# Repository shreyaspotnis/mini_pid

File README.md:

# mini_pid

A dual Proportional - Integral servo box

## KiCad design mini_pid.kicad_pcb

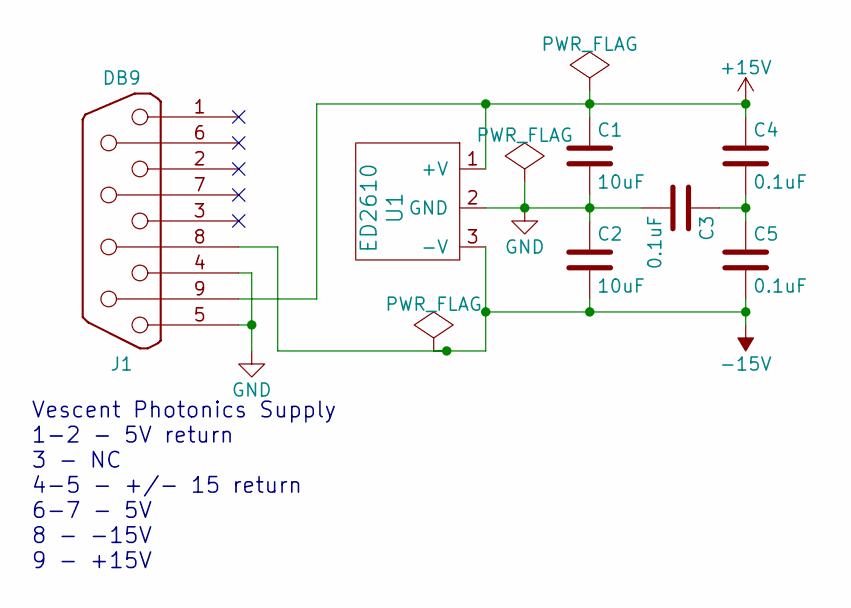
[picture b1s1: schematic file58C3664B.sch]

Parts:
C1, C2: 10uF; C_0805_HandSoldering
C3, C4, C5: 0.1uF; C_0805_HandSoldering
J1: DB9; DB9_Throughhole
U1: ED2610

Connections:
+15V: C1.1, C4.1, J1.9, U1.1 (+V); also elsewhere on the board
-15V: C2.2, C5.2, J1.8, U1.3 (-V); also elsewhere on the board
GND: C1.2, C2.1, C3.2, J1.4, J1.5, U1.2 (GND); also elsewhere on the board
unnamed: C3.1, C4.2, C5.1

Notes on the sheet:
Vescent Photonics Supply 1-2 - 5V return 3 - NC 4-5 - +/- 15 return 6-7 - 5V 8 - -15V 9 - +15V

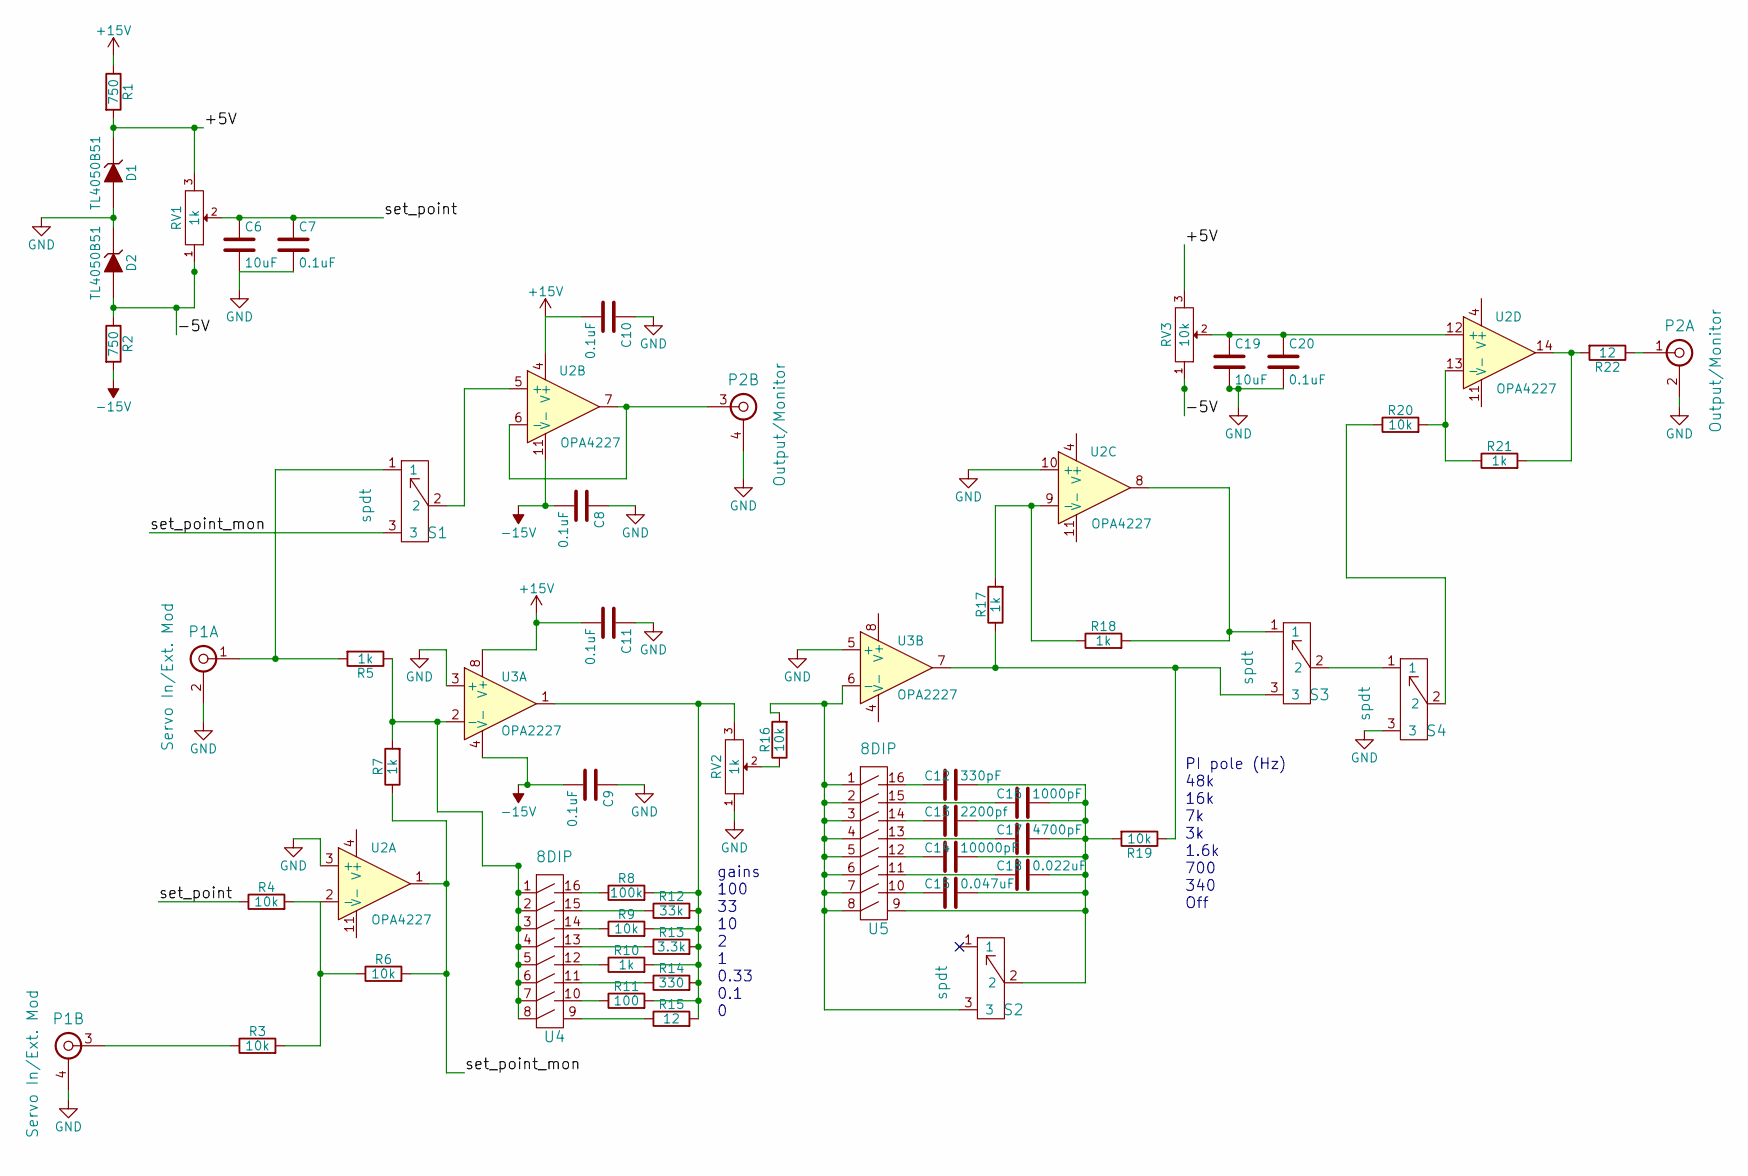
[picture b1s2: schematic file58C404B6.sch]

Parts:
C6, C19: 10uF; C_0805_HandSoldering
C7, C8, C9, C10, C11, C20: 0.1uF; C_0805_HandSoldering
C12: 330pF; C_0805_HandSoldering
C13: 2200pf; C_0805_HandSoldering
C14: 10000pF; C_0805_HandSoldering
C15: 0.047uF; C_0805_HandSoldering
C16: 1000pF; C_0805_HandSoldering
C17: 4700pF; C_0805_HandSoldering
C18: 0.022uF; C_0805_HandSoldering
D1, D2: TL4050B51; SOT-23
P1: Servo In/Ext. Mod; Dual-BNC-ARF2136
P2: Output/Monitor; Dual-BNC-ARF2136
R1, R2: 750; R_0805_HandSoldering
R3, R4, R6, R9, R16, R19, R20: 10k; R_0805_HandSoldering
R5, R7, R10, R17, R18, R21: 1k; R_0805_HandSoldering
R8: 100k; R_0805_HandSoldering
R11: 100; R_0805_HandSoldering
R12: 33k; R_0805_HandSoldering
R13: 3.3k; R_0805_HandSoldering
R14: 330; R_0805_HandSoldering
R15, R22: 12; R_0805_HandSoldering
RV1, RV2: 1k; VishaySpectrol536
RV3: 10k; VishaySpectrol536
S1, S2, S4: spdt; SPDT-Horizontal
S3: spdt; CJS-1200TB-SPDT
U2: OPA4227; SOIC-14_3.9x8.7mm_Pitch1.27mm
U3: OPA2227; SOIC-8_3.9x4.9mm_Pitch1.27mm
U4, U5: 8DIP; 8_POS_DIP_Switch

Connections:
+15V: C10.2, C11.2, R1.1, U2.4 (V+), U3.8 (V+); also elsewhere on the board
-15V: C8.2, C9.2, R2.2, U2.11 (V-), U3.4 (V-); also elsewhere on the board
/PI Circuit 1/+5V: D1.1 (K), R1.2, RV1.3, RV3.3
/PI Circuit 1/-5V: D2.2 (A), R2.1, RV1.1, RV3.1
/PI Circuit 1/set_point: C6.1, C7.1, R4.1, RV1.2
/PI Circuit 1/set_point_mon: R6.2, R7.1, S1.3, U2.1
GND: C6.2, C7.2, C8.1, C9.1, C10.1, C11.1, C19.2, C20.2, D1.2 (A), D2.1 (K), P1.2, P1.4, P2.2, P2.4, RV2.1, S4.3, U2.3 (+), U2.10 (+), U3.3 (+), U3.5 (+); also elsewhere on the board
unnamed: C12.1, C13.1, C14.1, C15.1, C16.1, C17.1, C18.1, R19.2, S2.2, U5.9
unnamed: C12.2, U5.16
unnamed: C13.2, U5.14
unnamed: C14.2, U5.12
unnamed: C15.2, U5.10
unnamed: C16.2, U5.15
unnamed: C17.2, U5.13
unnamed: C18.2, U5.11
unnamed: C19.1, C20.1, RV3.2, U2.12 (+)
unnamed: P1.1, R5.2, S1.1
unnamed: P1.3, R3.1
unnamed: P2.1, R22.1
unnamed: P2.3, U2.6 (-), U2.7
unnamed: R3.2, R4.2, R6.1, U2.2 (-)
unnamed: R5.1, R7.2, U3.2 (-), U4.1, U4.2, U4.3, U4.4, U4.5, U4.6, U4.7, U4.8
unnamed: R8.1, U4.16
unnamed: R9.1, U4.14
unnamed: R10.1, U4.12
unnamed: R8.2, R9.2, R10.2, R11.2, R12.2, R13.2, R14.2, R15.2, RV2.3, U3.1
unnamed: R11.1, U4.10
unnamed: R12.1, U4.15
unnamed: R13.1, U4.13
unnamed: R14.1, U4.11
unnamed: R15.1, U4.9
unnamed: R16.1, RV2.2
unnamed: R16.2, S2.3, U3.6 (-), U5.1, U5.2, U5.3, U5.4, U5.5, U5.6, U5.7, U5.8
unnamed: R17.1, R19.1, S3.3, U3.7
unnamed: R17.2, R18.1, U2.9 (-)
unnamed: R18.2, S3.1, U2.8
unnamed: R20.1, S4.2
unnamed: R20.2, R21.1, U2.13 (-)
unnamed: R21.2, R22.2, U2.14
unnamed: S1.2, U2.5 (+)
unnamed: S3.2, S4.1

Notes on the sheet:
gains 100 33 10 2 1 0.33 0.1 0
PI pole (Hz) 48k 16k 7k 3k 1.6k 700 340 Off

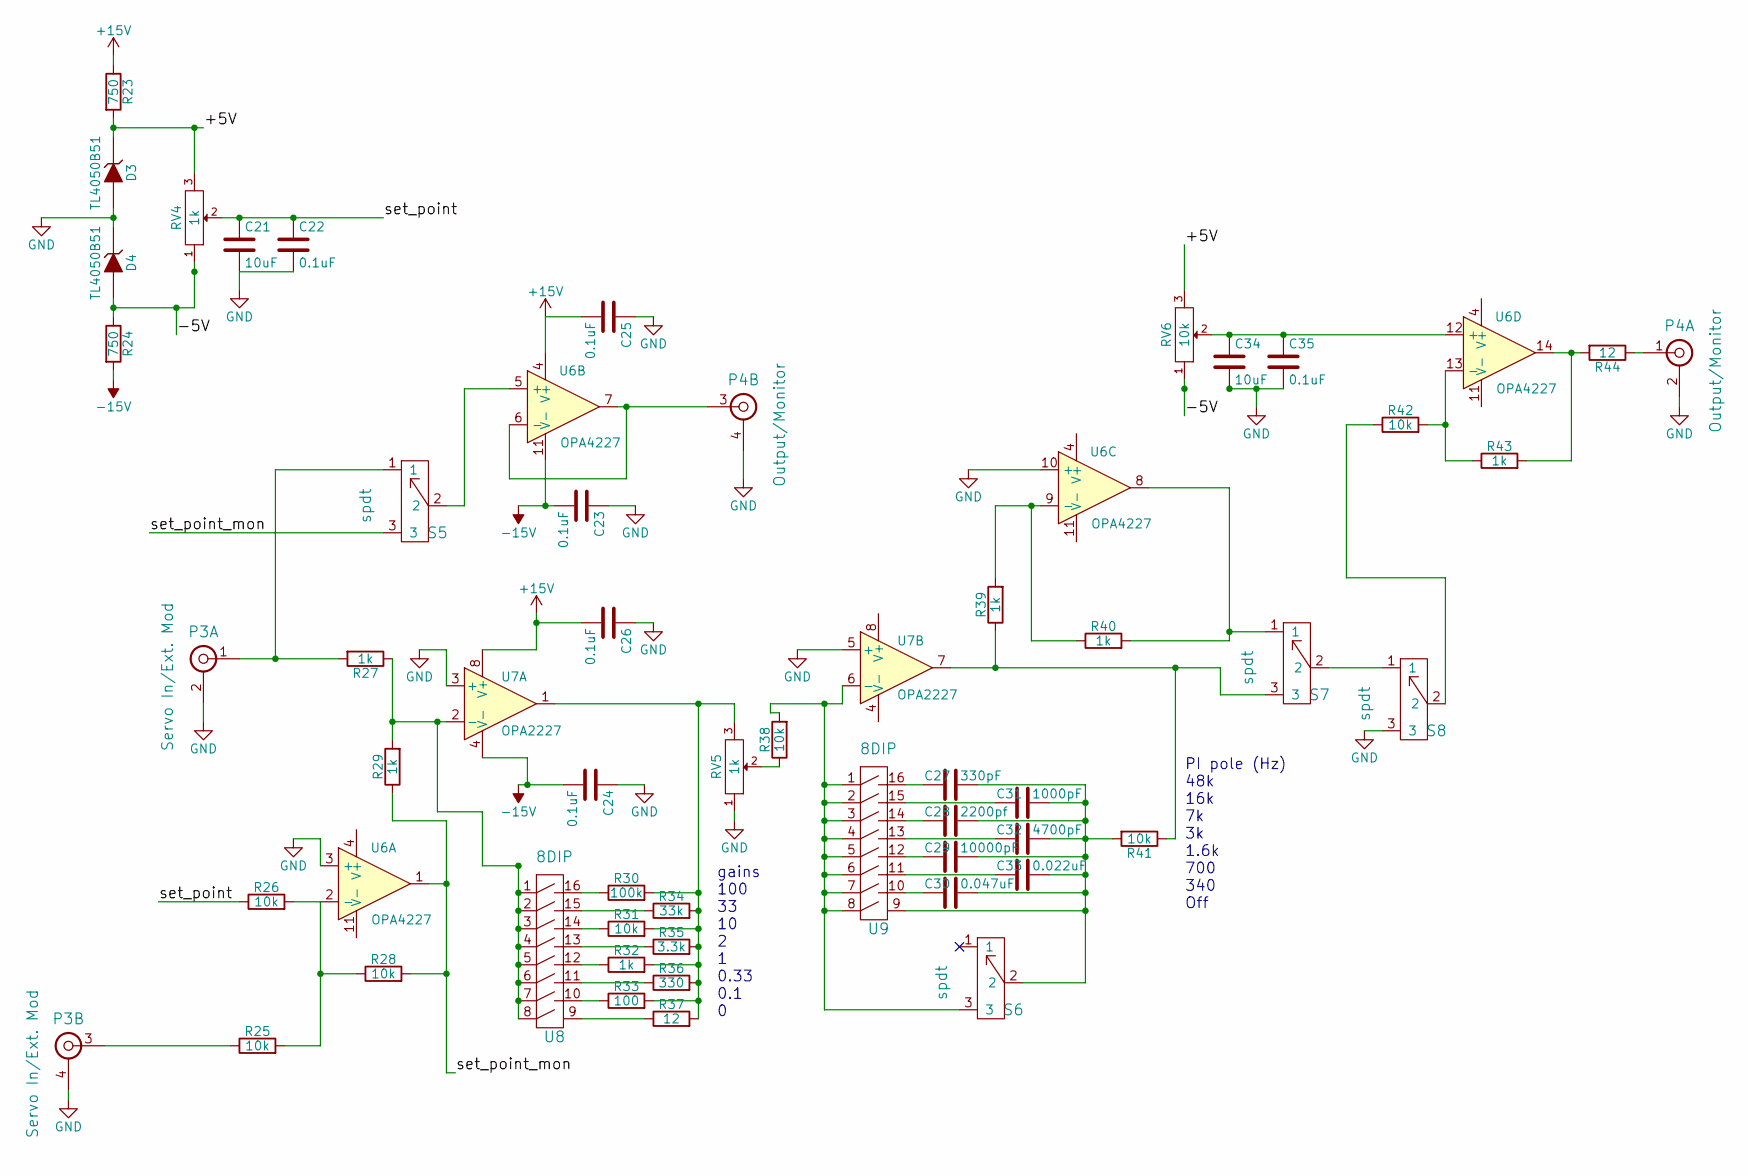
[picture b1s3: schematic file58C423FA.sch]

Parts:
C21, C34: 10uF; C_0805_HandSoldering
C22, C23, C24, C25, C26, C35: 0.1uF; C_0805_HandSoldering
C27: 330pF; C_0805_HandSoldering
C28: 2200pf; C_0805_HandSoldering
C29: 10000pF; C_0805_HandSoldering
C30: 0.047uF; C_0805_HandSoldering
C31: 1000pF; C_0805_HandSoldering
C32: 4700pF; C_0805_HandSoldering
C33: 0.022uF; C_0805_HandSoldering
D3, D4: TL4050B51; SOT-23
P3: Servo In/Ext. Mod; Dual-BNC-ARF2136
P4: Output/Monitor; Dual-BNC-ARF2136
R23, R24: 750; R_0805_HandSoldering
R25, R26, R28, R31, R38, R41, R42: 10k; R_0805_HandSoldering
R27, R29, R32, R39, R40, R43: 1k; R_0805_HandSoldering
R30: 100k; R_0805_HandSoldering
R33: 100; R_0805_HandSoldering
R34: 33k; R_0805_HandSoldering
R35: 3.3k; R_0805_HandSoldering
R36: 330; R_0805_HandSoldering
R37, R44: 12; R_0805_HandSoldering
RV4, RV5: 1k; VishaySpectrol536
RV6: 10k; VishaySpectrol536
S5, S6, S8: spdt; SPDT-Horizontal
S7: spdt; CJS-1200TB-SPDT
U6: OPA4227; SOIC-14_3.9x8.7mm_Pitch1.27mm
U7: OPA2227; SOIC-8_3.9x4.9mm_Pitch1.27mm
U8, U9: 8DIP; 8_POS_DIP_Switch

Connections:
+15V: C25.2, C26.2, R23.1, U6.4 (V+), U7.8 (V+); also elsewhere on the board
-15V: C23.2, C24.2, R24.2, U6.11 (V-), U7.4 (V-); also elsewhere on the board
/PI Circuit 2/+5V: D3.1 (K), R23.2, RV4.3, RV6.3
/PI Circuit 2/-5V: D4.2 (A), R24.1, RV4.1, RV6.1
/PI Circuit 2/set_point: C21.1, C22.1, R26.1, RV4.2
/PI Circuit 2/set_point_mon: R28.2, R29.1, S5.3, U6.1
GND: C21.2, C22.2, C23.1, C24.1, C25.1, C26.1, C34.2, C35.2, D3.2 (A), D4.1 (K), P3.2, P3.4, P4.2, P4.4, RV5.1, S8.3, U6.3 (+), U6.10 (+), U7.3 (+), U7.5 (+); also elsewhere on the board
unnamed: C27.1, C28.1, C29.1, C30.1, C31.1, C32.1, C33.1, R41.2, S6.2, U9.9
unnamed: C27.2, U9.16
unnamed: C28.2, U9.14
unnamed: C29.2, U9.12
unnamed: C30.2, U9.10
unnamed: C31.2, U9.15
unnamed: C32.2, U9.13
unnamed: C33.2, U9.11
unnamed: C34.1, C35.1, RV6.2, U6.12 (+)
unnamed: P3.1, R27.2, S5.1
unnamed: P3.3, R25.1
unnamed: P4.1, R44.1
unnamed: P4.3, U6.6 (-), U6.7
unnamed: R25.2, R26.2, R28.1, U6.2 (-)
unnamed: R27.1, R29.2, U7.2 (-), U8.1, U8.2, U8.3, U8.4, U8.5, U8.6, U8.7, U8.8
unnamed: R30.1, U8.16
unnamed: R30.2, R31.2, R32.2, R33.2, R34.2, R35.2, R36.2, R37.2, RV5.3, U7.1
unnamed: R31.1, U8.14
unnamed: R32.1, U8.12
unnamed: R33.1, U8.10
unnamed: R34.1, U8.15
unnamed: R35.1, U8.13
unnamed: R36.1, U8.11
unnamed: R37.1, U8.9
unnamed: R38.1, RV5.2
unnamed: R38.2, S6.3, U7.6 (-), U9.1, U9.2, U9.3, U9.4, U9.5, U9.6, U9.7, U9.8
unnamed: R39.1, R41.1, S7.3, U7.7
unnamed: R39.2, R40.1, U6.9 (-)
unnamed: R40.2, S7.1, U6.8
unnamed: R42.1, S8.2
unnamed: R42.2, R43.1, U6.13 (-)
unnamed: R43.2, R44.2, U6.14
unnamed: S5.2, U6.5 (+)
unnamed: S7.2, S8.1

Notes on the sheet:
gains 100 33 10 2 1 0.33 0.1 0
PI pole (Hz) 48k 16k 7k 3k 1.6k 700 340 Off

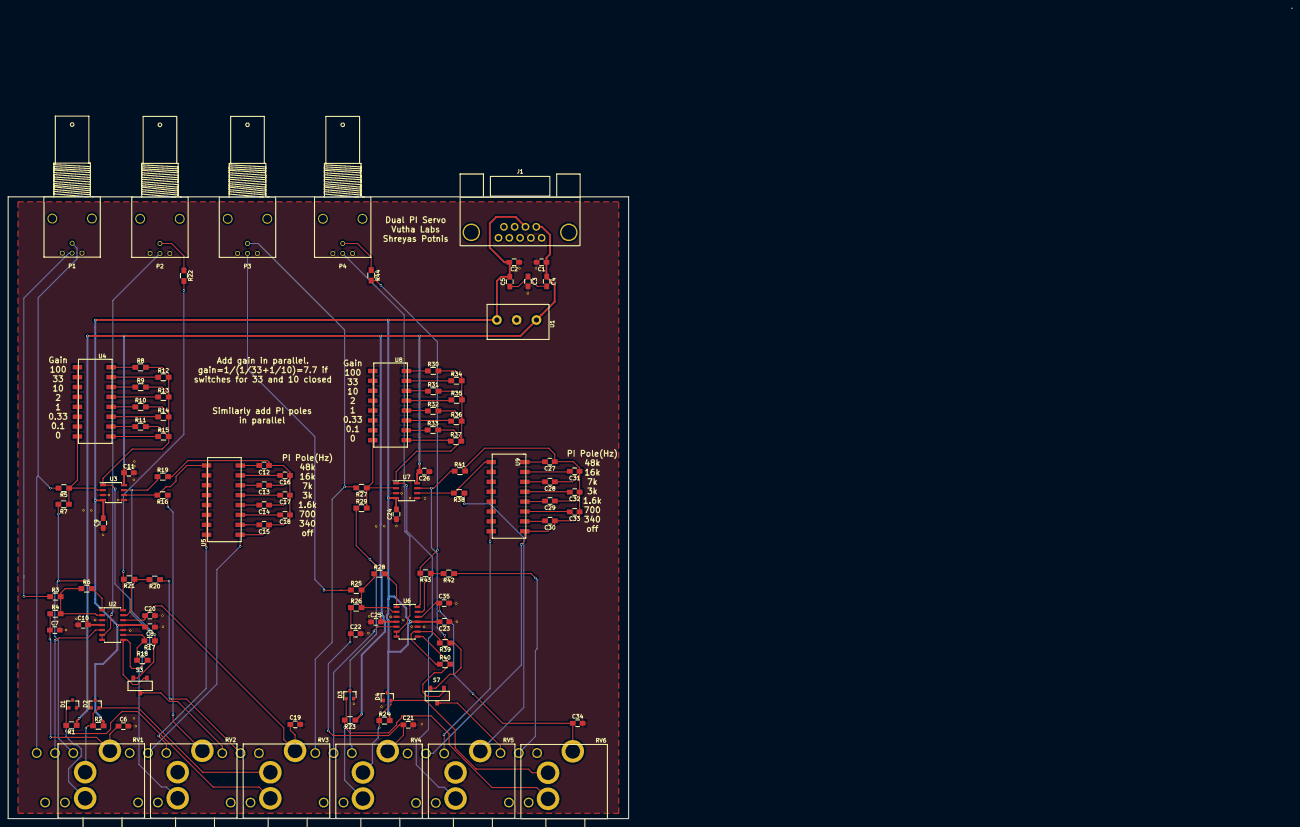
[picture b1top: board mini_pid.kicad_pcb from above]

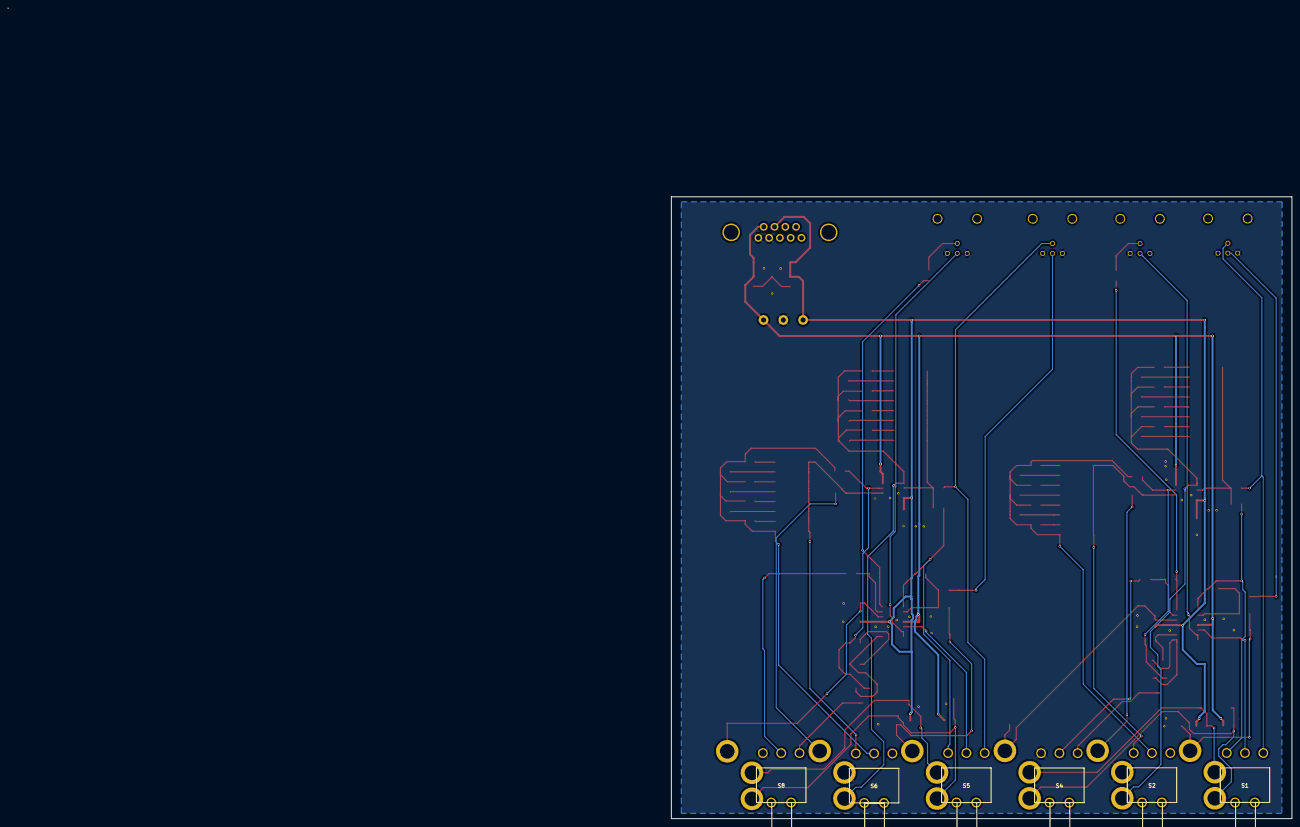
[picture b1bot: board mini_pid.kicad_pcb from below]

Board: 2 copper layers, 159.3 x 159.7 mm, 111 parts (6 on the bottom side), 80 nets.

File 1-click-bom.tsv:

References	Qty	Description
C1, C2, C19, C6, C34, C21	6	C 10uF Unpolarized capacitor 0805 HandSoldering
C4, C5, C3, C10, C8, C11, C9, C20, C7, C25, C23, C26, C24, C35, C22	15	C 0.1uF Unpolarized capacitor 0805 HandSoldering
C12, C27	2	C 330pF Unpolarized capacitor 0805 HandSoldering
C13, C28	2	C 2200pf Unpolarized capacitor 0805 HandSoldering
C14, C29	2	C 10000pF Unpolarized capacitor 0805 HandSoldering
C15, C30	2	C 0.047uF Unpolarized capacitor 0805 HandSoldering
C16, C31	2	C 1000pF Unpolarized capacitor 0805 HandSoldering
C17, C32	2	C 4700pF Unpolarized capacitor 0805 HandSoldering
C18, C33	2	C 0.022uF Unpolarized capacitor 0805 HandSoldering
D1, D2, D3, D4	4	TL4050B51 Precision 5V reference SOT-23
J1	1	DB9 Throughhole
P1, P3	2	Dual-BNC Servo In/Ext. Mod Dual-BNC-ARF2136
P2, P4	2	Dual-BNC Output/Monitor Dual-BNC-ARF2136
R1, R2, R23, R24	4	R 750 Resistor 0805 HandSoldering
R7, R5, R10, R17, R18, R21, R29, R27, R32, R39, R40, R43	12	R 1k Resistor 0805 HandSoldering
R8, R30	2	R 100k Resistor 0805 HandSoldering
R9, R16, R3, R4, R6, R19, R20, R31, R38, R25, R26, R28, R41, R42	14	R 10k Resistor 0805 HandSoldering
R11, R33	2	R 100 Resistor 0805 HandSoldering
R12, R34	2	R 33k Resistor 0805 HandSoldering
R13, R35	2	R 3.3k Resistor 0805 HandSoldering
R14, R36	2	R 330 Resistor 0805 HandSoldering
R15, R22, R37, R44	4	R 12 Resistor 0805 HandSoldering
RV2, RV1, RV5, RV4	4	POT-RESCUE-mini pid 1k VishaySpectrol536
RV3, RV6	2	POT-RESCUE-mini pid 10k VishaySpectrol536
S1, S2, S4, S5, S6, S8	6	spdt SPDT-Horizontal
S3, S7	2	spdt CJS-1200TB-SPDT
U1	1	ED2610
U2, U6	2	OPA4227 Quad Op amp. SOIC-14 3.9x8.7mm Pitch1.27mm
U3, U7	2	OPA2227 Dual Op amp (low power) SOIC-8 3.9x4.9mm Pitch1.27mm
U4, U5, U8, U9	4	8DIP 8 POS DIP Switch

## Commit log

2017-03-07 :octocat: Added .gitattributes & .gitignore files
2017-03-07 Started layout out traces
2017-03-08 Layout for old version completed
2017-03-09 Project is now dual PID :)
2017-03-13 Schematic complete
2017-03-13 Made both circiuts identical
2017-03-13 Footprints assigned
2017-03-13 Reset board layout
2017-03-13 Board connectors placed
2017-03-13 PI circuit 1 done
2017-03-14 Track routing done.
2017-03-14 Added ground planes, fixed unconnected nets.
2017-03-14 Almost done, but rewiring for optimization
2017-03-14 Spaced out components
2017-03-14 Interactive routing FTW. PI circuit 1 done.
2017-03-14 Gerber and drill files created.
